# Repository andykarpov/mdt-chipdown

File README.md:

# MicroDEXED Touch Chipdown custom edition

This is an attempt to create a custom PCB of the MicroDEXED Touch (MDT) project to satisfy my own requirements:

- No modules, all chips should be soldered on PCB
- Avoid THT components as much as possible

**Warning! Work in progress. The revB is untested and unreleased yet.**

- Current tested revision: **revA**
- Current dev revision: **revB**

## PCB changelog & ERRATA:

- revA - initial revision
    - Note: Jumpers to select MIDI IN/OUT standard should be removed, instead of them please use 0 Ohm resistors
    - Latest revA contains the following changes: jumpers replaced with solder jumpers
    - The overall display height is slightly higher than expected. Please use 8.5mm standoffs for it. Also the plastic housing from the display pin headers should be removed and the pin height should be reduced to fit the desired connection height of 8.5mm
- revB:
    - 4-layers PCB
    - Replaced teensy module with a set of chips
    - Added additional SD card
    - Added additional LED from the supplementary MCU
    - Changed USB Host power path

## Rev.A Renders

## Case for rev.A

## Rev.B Renders

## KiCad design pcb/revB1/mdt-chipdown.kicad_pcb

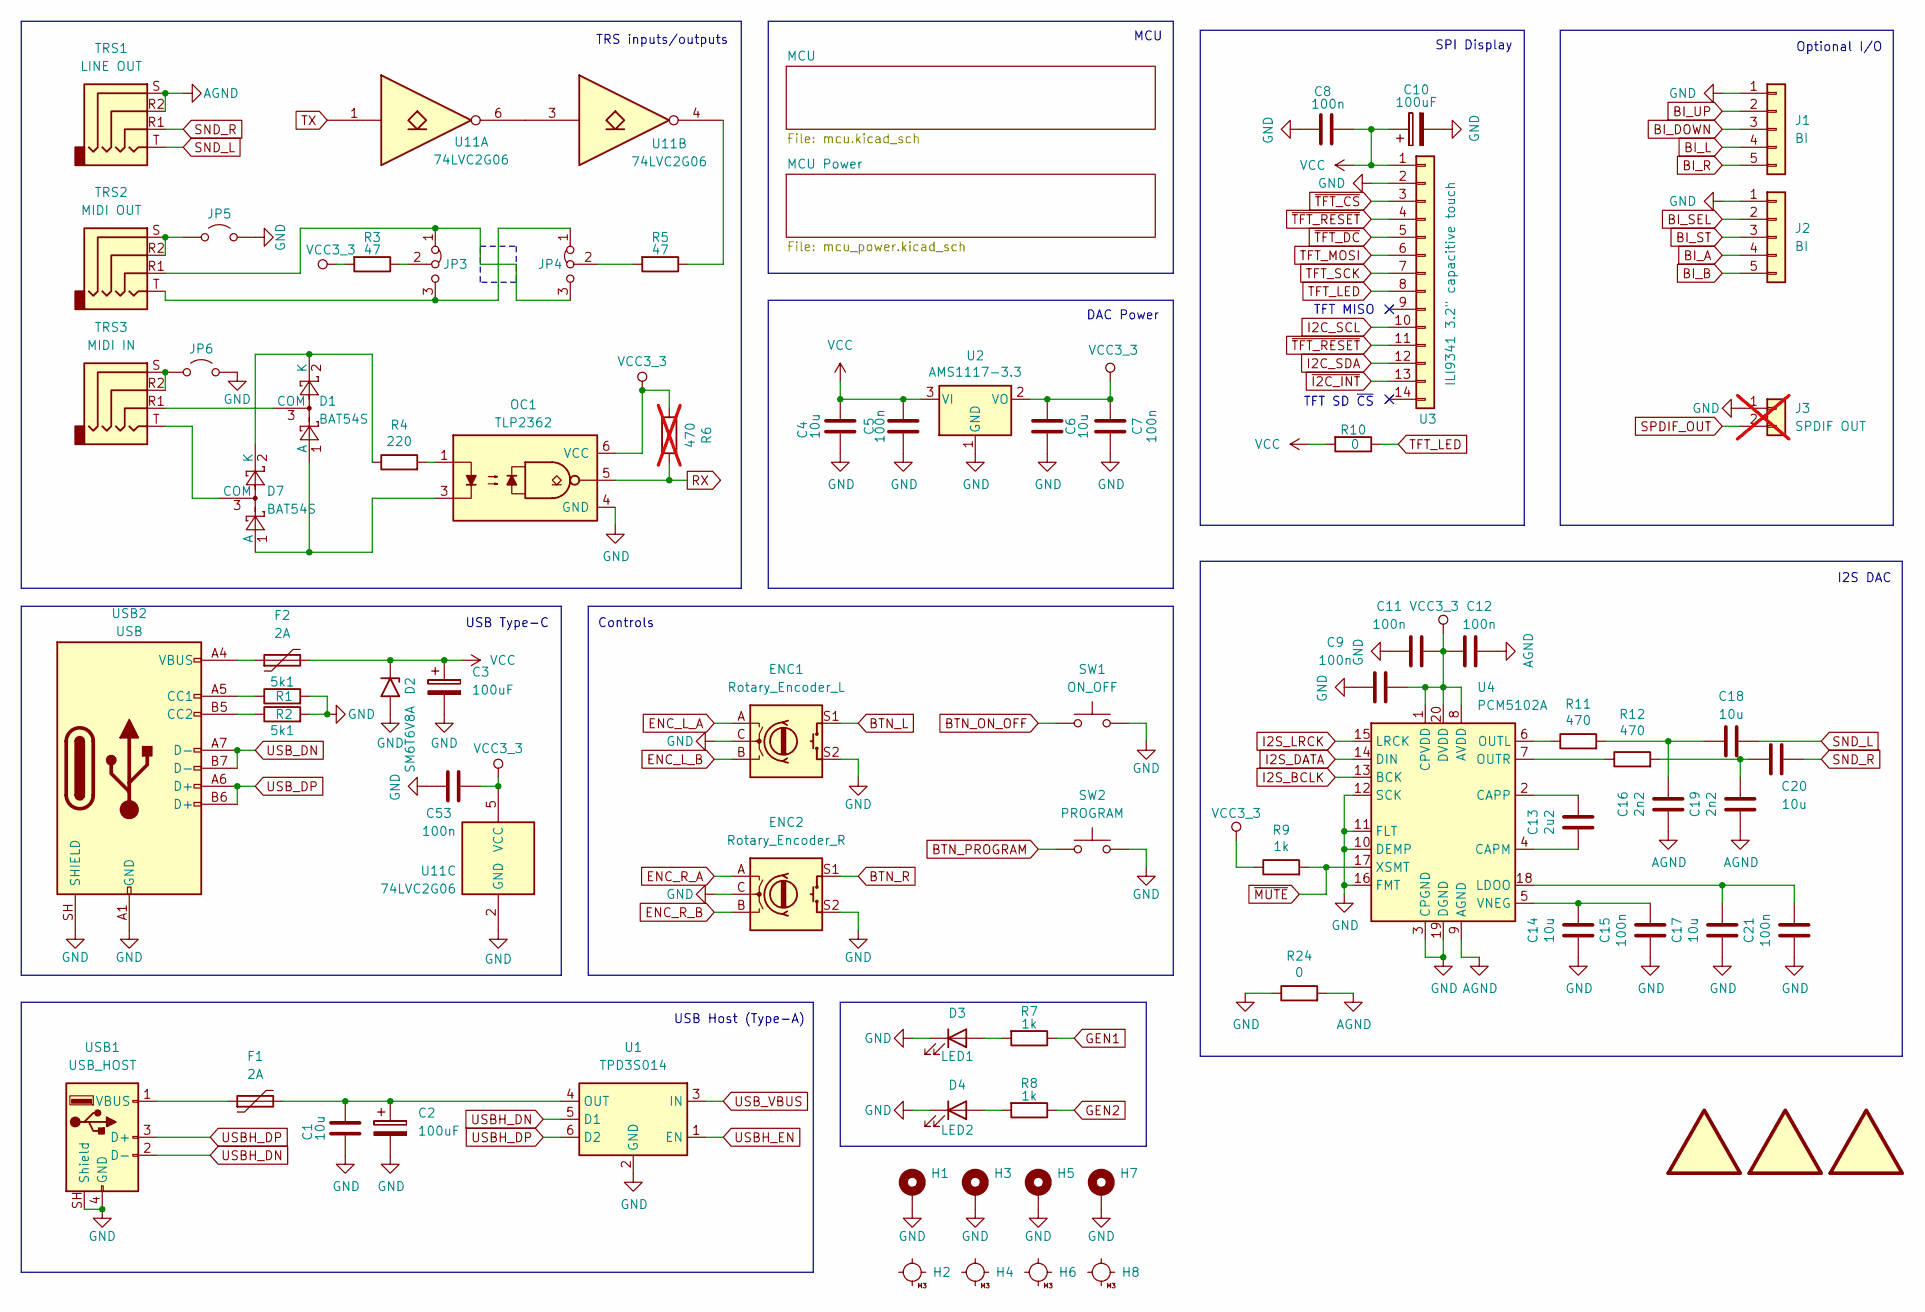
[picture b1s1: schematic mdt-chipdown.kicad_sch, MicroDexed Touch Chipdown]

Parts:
C1, C4, C6, C14, C17, C18, C20: 10u; C_0805_2012Metric_Pad1.18x1.45mm_HandSolder; LCSC C15850
C2, C3: 100uF; CP_EIA-7343-31_Kemet-D_HandSolder; LCSC C2749
C5, C7, C8, C9, C11, C12, C15, C21, C53: 100n; C_0805_2012Metric_Pad1.18x1.45mm_HandSolder; LCSC C1711
C10: 100uF; CP_EIA-6032-28_Kemet-C_HandSolder; LCSC C8649
C13: 2u2; C_0805_2012Metric_Pad1.18x1.45mm_HandSolder; LCSC C19110
C16, C19: 2n2; C_0805_2012Metric_Pad1.18x1.45mm_HandSolder; LCSC C1728
D1, D7: BAT54S; SOT-23_Handsoldering; LCSC C7420333
D2: SM6T6V8A; D_SMB_Handsoldering; LCSC C511038
D3: LED1; LED_Indicator_D3.0mm_W4.6mm_L6.5mm; LCSC C17683617
D4: LED2; LED_Indicator_D3.0mm_W4.6mm_L6.5mm; LCSC C473837
ENC1: Rotary_Encoder_L; RotaryEncoder_Alps_EC11E-Switch_Vertical_H20mm; LCSC C7435302
ENC2: Rotary_Encoder_R; RotaryEncoder_Alps_EC11E-Switch_Vertical_H20mm; LCSC C7435302
F1, F2: 2A; Fuse_1812_4532Metric_Pad1.30x3.40mm_HandSolder; LCSC C20812
H1, H3, H5, H7: MountingHole_Pad; MountingHole_3mm_Pad_Via
H2, H4, H6, H8: MountingHole_M3
J1, J2: BI; PinHeader_1x05_P2.54mm_Vertical; LCSC C5156614
J3: SPDIF OUT; Pin_Header_Straight_1x02; Part Number 1-0201FBV0T; LCSC C5360898; not fitted
JP3, JP4: Jumper_3_Bridged12; SolderJumper-3_P1.3mm_Bridged12_RoundedPad1.0x1.5mm
JP5: Jumper_2_Open; SolderJumper-2_P1.3mm_Bridged_RoundedPad1.0x1.5mm
JP6: Jumper_2_Open; SolderJumper-2_P1.3mm_Open_RoundedPad1.0x1.5mm
LOGO1: logo; microDXD_logo12
LOGO2: logo; andy_karpov_logo5_silk
LOGO3: logo; KiCad-Logo2_6mm_SilkScreen
OC1: TLP2362; SO-5-6_4.55x3.7mm_P1.27mm; LCSC C37658
R1, R2: 5k1; R_0805_2012Metric_Pad1.20x1.40mm_HandSolder; LCSC C26023
R3, R5: 47; R_0805_2012Metric_Pad1.20x1.40mm_HandSolder; LCSC C25315
R4: 220; R_0805_2012Metric_Pad1.20x1.40mm_HandSolder; LCSC C17557
R6: 470; R_0805_2012Metric_Pad1.20x1.40mm_HandSolder; LCSC C17710; not fitted
R7, R8, R9: 1k; R_0805_2012Metric_Pad1.20x1.40mm_HandSolder; LCSC C17513
R10: 0; R_0805_2012Metric_Pad1.20x1.40mm_HandSolder; LCSC C17477
R11, R12: 470; R_0805_2012Metric_Pad1.20x1.40mm_HandSolder; LCSC C17710
R24: 0; R_0805_2012Metric_Pad1.20x1.40mm_HandSolder; LCSC C17513
SW1: ON_OFF; Push_PTH_RA_8-020_h7.5mm; LCSC C125050
SW2: PROGRAM; Push_PTH_RA_8-020_h7.5mm; LCSC C125050
TRS1: LINE OUT; AUDIO_JACK_3.5MM_SMD_TRRS_rounded_mixed; LCSC C53447038
TRS2: MIDI OUT; AUDIO_JACK_3.5MM_SMD_TRRS_rounded_mixed; LCSC C53447038
TRS3: MIDI IN; AUDIO_JACK_3.5MM_SMD_TRRS_rounded_mixed; LCSC C53447038
U1: TPD3S014; SOT-23-6_Handsoldering; LCSC C87384
U2: AMS1117-3.3; TO-252-2; LCSC C41414107
U3: ILI9341 3.2" capacitive touch; PinSocket_1x14_P2.54mm_Vertical; LCSC C124407
U4: PCM5102A; TSSOP-20_4.4x6.5mm_P0.65mm; LCSC C107671
U11: 74LVC2G06; SOT-23-6_Handsoldering; LCSC C402162
USB1: USB_HOST; USB_A_Molex_67643_Horizontal; LCSC C2346
USB2: USB; USB_C_Receptacle_G-Switch_GT-USB-7010ASV; LCSC C165948

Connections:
AGND: C12.1, C16.1, C19.1, R24.2, TRS1.R2, TRS1.S, U4.9 (AGND)
BI_A: J2.4; also elsewhere on the board
BI_B: J2.5; also elsewhere on the board
BI_DOWN: J1.3; also elsewhere on the board
BI_L: J1.4; also elsewhere on the board
BI_R: J1.5; also elsewhere on the board
BI_SEL: J2.2; also elsewhere on the board
BI_ST: J2.3; also elsewhere on the board
BI_UP: J1.2; also elsewhere on the board
BTN_L: ENC1.S1; also elsewhere on the board
BTN_ON_OFF: SW1.1; also elsewhere on the board
BTN_PROGRAM: SW2.1; also elsewhere on the board
BTN_R: ENC2.S1; also elsewhere on the board
ENC_L_A: ENC1.A; also elsewhere on the board
ENC_L_B: ENC1.B; also elsewhere on the board
ENC_R_A: ENC2.A; also elsewhere on the board
ENC_R_B: ENC2.B; also elsewhere on the board
GEN1: R7.1; also elsewhere on the board
GEN2: R8.1; also elsewhere on the board
GND: C1.2, C2.2, C3.2, C4.2, C5.2, C6.2, C7.2, C8.2, C9.2, C10.2, C11.2, C14.1, C15.1, C17.1, C21.1, C53.2, D2.2 (A2), D3.1 (K), D4.1 (K), ENC1.C, ENC1.S2, ENC2.C, ENC2.S2, H1.1 (1_1), H3.1 (1_1), H5.1 (1_1), H7.1 (1_1), J1.1, J2.1, J3.1, JP5.2 (B), JP6.2 (B), OC1.4 (GND), R1.2, R2.2, R24.1, SW1.2, SW2.2, U1.2 (GND), U2.1 (GND), U3.2, U4.3 (CPGND), U4.10 (DEMP), U4.11 (FLT), U4.12 (SCK), U4.16 (FMT), U4.19 (DGND), U11.2 (GND), USB1.4 (GND), USB1.SH (Shield), USB2.A1 (GND), USB2.A12 (GND), USB2.B1 (GND), USB2.B12 (GND), USB2.SH (SHIELD); also elsewhere on the board
I2C_SCL: U3.10; also elsewhere on the board
I2C_SDA: U3.12; also elsewhere on the board
I2S_BCLK: U4.13 (BCK); also elsewhere on the board
I2S_DATA: U4.14 (DIN); also elsewhere on the board
I2S_LRCK: U4.15 (LRCK); also elsewhere on the board
unnamed: C16.2, C18.2, R11.2
unnamed: C19.2, C20.2, R12.2
unnamed: D1.1 (A), D7.1 (A), OC1.3
unnamed: D1.3 (COM), TRS3.R1
unnamed: D1.2 (K), D7.2 (K), R4.1
unnamed: D3.2 (A), R7.2
unnamed: D4.2 (A), R8.2
unnamed: D7.3 (COM), TRS3.T
unnamed: F2.1, USB2.A4 (VBUS), USB2.A9 (VBUS), USB2.B4 (VBUS), USB2.B9 (VBUS)
unnamed: JP3.1 (A), JP4.3 (B), TRS2.R1
unnamed: JP3.3 (B), JP4.1 (A), TRS2.T
unnamed: JP3.2 (C), R3.1
unnamed: JP4.2 (C), R5.2
unnamed: JP5.1 (A), TRS2.R2, TRS2.S
unnamed: JP6.1 (A), TRS3.R2, TRS3.S
unnamed: OC1.1, R4.2
unnamed: R5.1, U11.4
unnamed: C1.1, C2.1, F1.2, U1.4 (OUT)
unnamed: C13.1, U4.4 (CAPM)
unnamed: C13.2, U4.2 (CAPP)
unnamed: C17.2, C21.2, U4.18 (LDOO)
unnamed: R11.1, U4.6 (OUTL)
unnamed: R12.1, U4.7 (OUTR)
unnamed: C14.2, C15.2, U4.5 (VNEG)
unnamed: U11.3, U11.6
unnamed: F1.1, USB1.1 (VBUS)
unnamed: R1.1, USB2.A5 (CC1)
unnamed: R2.1, USB2.B5 (CC2)
RX: OC1.5, R6.2; also elsewhere on the board
SND_L: C18.1, TRS1.T
SND_R: C20.1, TRS1.R1
SPDIF_OUT: J3.2; also elsewhere on the board
TFT_LED: R10.1, U3.8
TFT_MOSI: U3.6; also elsewhere on the board
TFT_SCK: U3.7; also elsewhere on the board
TX: U11.1; also elsewhere on the board
USBH_DN: U1.5 (D1), USB1.2 (D-); also elsewhere on the board
USBH_DP: U1.6 (D2), USB1.3 (D+); also elsewhere on the board
USBH_EN: U1.1 (EN); also elsewhere on the board
USB_DN: USB2.A7 (D-), USB2.B7 (D-); also elsewhere on the board
USB_DP: USB2.A6 (D+), USB2.B6 (D+); also elsewhere on the board
USB_VBUS: U1.3 (IN); also elsewhere on the board
VCC: C3.1, C4.1, C5.1, C8.1, C10.1, D2.1 (A1), F2.2, R10.2, U2.3 (VI), U3.1; also elsewhere on the board
VCC3_3: C6.1, C7.1, C9.1, C11.1, C12.2, C53.1, OC1.6 (VCC), R3.2, R6.1, R9.1, U2.2 (VO), U4.1 (CPVDD), U4.8 (AVDD), U4.20 (DVDD), U11.5 (VCC)
~I2C_INT: U3.13; also elsewhere on the board
~MUTE: R9.2, U4.17 (XSMT); also elsewhere on the board
~TFT_CS: U3.3; also elsewhere on the board
~TFT_DC: U3.5; also elsewhere on the board
~TFT_RESET: U3.4, U3.11; also elsewhere on the board

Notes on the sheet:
TRS inputs/outputs
I2S DAC
TFT SD ~{CS}
DAC Power
MCU
Optional I/O
SPI Display
TFT MISO
USB Host (Type-A)
Controls
USB Type-C

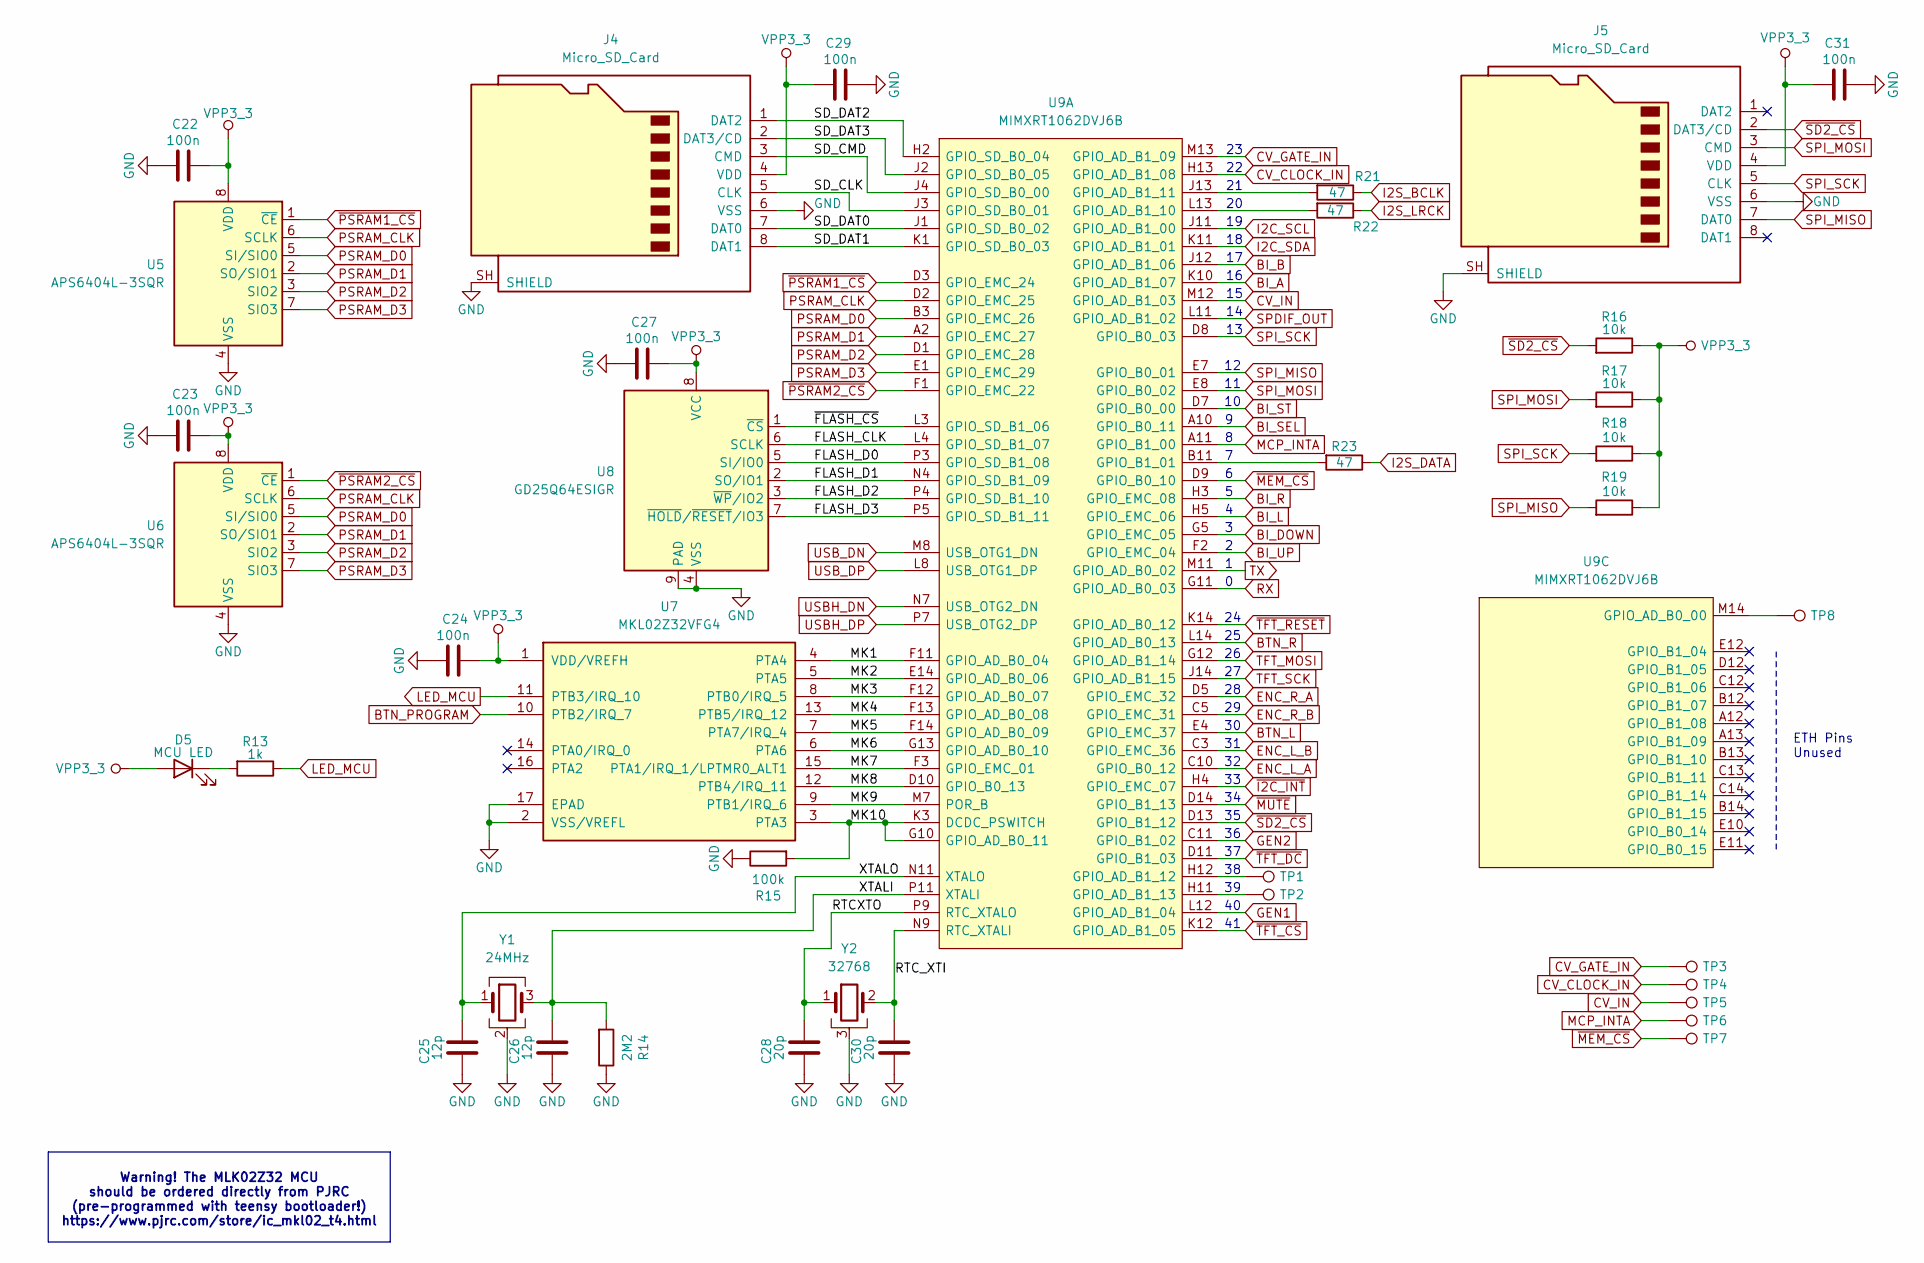
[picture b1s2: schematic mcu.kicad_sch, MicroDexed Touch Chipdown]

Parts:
C22, C23, C24, C27, C29, C31: 100n; C_0805_2012Metric_Pad1.18x1.45mm_HandSolder; LCSC C1711
C25, C26: 12p; C_0805_2012Metric_Pad1.18x1.45mm_HandSolder; LCSC C152848
C28, C30: 20p; C_0805_2012Metric_Pad1.18x1.45mm_HandSolder; LCSC C1727
D5: MCU LED; LED_Indicator_D3.0mm_W4.6mm_L6.5mm; LCSC C19188468
J4, J5: Micro_SD_Card; GCT-MEM2055-00-190-01-A; LCSC C91145
R13: 1k; R_0805_2012Metric_Pad1.20x1.40mm_HandSolder; LCSC C17513
R14: 2M2; R_0805_2012Metric_Pad1.20x1.40mm_HandSolder; LCSC C26113
R15: 100k; R_0805_2012Metric_Pad1.20x1.40mm_HandSolder; LCSC C25611
R16, R17, R18, R19: 10k; R_0805_2012Metric_Pad1.20x1.40mm_HandSolder; LCSC C17414
R21, R22, R23: 47; R_0805_2012Metric_Pad1.20x1.40mm_HandSolder; LCSC C25315
TP1: GPIO_AD_B1_12; TestPoint_Pad_2.0x2.0mm
TP2: GPIO_AD_B1_13; TestPoint_Pad_2.0x2.0mm
TP3: CV GATE IN; TestPoint_Pad_2.0x2.0mm
TP4: CV CLOCK IN; TestPoint_Pad_2.0x2.0mm
TP5: CV IN; TestPoint_Pad_2.0x2.0mm
TP6: MCP INTA; TestPoint_Pad_2.0x2.0mm
TP7: MEM CS; TestPoint_Pad_2.0x2.0mm
TP8: GPIO_AD_B0_00; TestPoint_Pad_2.0x2.0mm
U5, U6: APS6404L-3SQR; SOIC-8_3.9x4.9mm_P1.27mm; LCSC C5333729
U7: MKL02Z32VFG4; QFN-16-1EP_3x3mm_P0.5mm_EP1.9x1.9mm; LCSC C2056583
U8: GD25Q64ESIGR; SOIC-8_5.3x5.3mm_P1.27mm; LCSC C2831359
U9: MIMXRT1062DVJ6B; BGA196C80P14X14_1200X1200X152; Mouser Part Number 771-MIMXRT1062DVJ6B
Y1: 24MHz; Crystal_SMD_3225-4Pin_3.2x2.5mm_HandSoldering; LCSC C15643
Y2: 32768; Crystal_C26-LF_D2.1mm_L6.5mm_Horizontal_1EP_style2; LCSC C2236

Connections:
/MCU/FLASH_CLK: U8.6 (SCLK), U9.L4 (GPIO_SD_B1_07)
/MCU/FLASH_D0: U8.5 (SI/IO0), U9.P3 (GPIO_SD_B1_08)
/MCU/FLASH_D1: U8.2 (SO/IO1), U9.N4 (GPIO_SD_B1_09)
/MCU/FLASH_D2: U8.3 (~WP/IO2), U9.P4 (GPIO_SD_B1_10)
/MCU/FLASH_D3: U8.7 (~HOLD/~RESET/IO3), U9.P5 (GPIO_SD_B1_11)
/MCU/MK1: U7.4 (PTA4), U9.F11 (GPIO_AD_B0_04)
/MCU/MK2: U7.5 (PTA5), U9.E14 (GPIO_AD_B0_06)
/MCU/MK3: U7.8 (PTB0/IRQ_5), U9.F12 (GPIO_AD_B0_07)
/MCU/MK4: U7.13 (PTB5/IRQ_12), U9.F13 (GPIO_AD_B0_08)
/MCU/MK5: U7.7 (PTA7/IRQ_4), U9.F14 (GPIO_AD_B0_09)
/MCU/MK6: U7.6 (PTA6), U9.G13 (GPIO_AD_B0_10)
/MCU/MK7: U7.15 (PTA1/IRQ_1/LPTMR0_ALT1), U9.F3 (GPIO_EMC_01)
/MCU/MK8: U7.12 (PTB4/IRQ_11), U9.D10 (GPIO_B0_13)
/MCU/MK9: U7.9 (PTB1/IRQ_6), U9.M7 (POR_B)
/MCU/MK10: R15.2, U7.3 (PTA3), U9.G10 (GPIO_AD_B0_11), U9.K3 (DCDC_PSWITCH)
/MCU/RTCXTO: C28.1, U9.P9 (RTC_XTALO), Y2.1
/MCU/RTC_XTI: C30.1, U9.N9 (RTC_XTALI), Y2.2
/MCU/SD_CLK: J4.5 (CLK), U9.J3 (GPIO_SD_B0_01)
/MCU/SD_CMD: J4.3 (CMD), U9.J4 (GPIO_SD_B0_00)
/MCU/SD_DAT0: J4.7 (DAT0), U9.J1 (GPIO_SD_B0_02)
/MCU/SD_DAT1: J4.8 (DAT1), U9.K1 (GPIO_SD_B0_03)
/MCU/SD_DAT2: J4.1 (DAT2), U9.H2 (GPIO_SD_B0_04)
/MCU/SD_DAT3: J4.2 (DAT3/CD), U9.J2 (GPIO_SD_B0_05)
/MCU/XTALI: C26.1, R14.2, U9.P11 (XTALI), Y1.3
/MCU/XTALO: C25.1, U9.N11 (XTALO), Y1.1
/MCU/~FLASH_CS: U8.1 (~CS), U9.L3 (GPIO_SD_B1_06)
BI_A: U9.K10 (GPIO_AD_B1_07); also elsewhere on the board
BI_B: U9.J12 (GPIO_AD_B1_06); also elsewhere on the board
BI_DOWN: U9.G5 (GPIO_EMC_05); also elsewhere on the board
BI_L: U9.H5 (GPIO_EMC_06); also elsewhere on the board
BI_R: U9.H3 (GPIO_EMC_08); also elsewhere on the board
BI_SEL: U9.A10 (GPIO_B0_11); also elsewhere on the board
BI_ST: U9.D7 (GPIO_B0_00); also elsewhere on the board
BI_UP: U9.F2 (GPIO_EMC_04); also elsewhere on the board
BTN_L: U9.E4 (GPIO_EMC_37); also elsewhere on the board
BTN_PROGRAM: U7.10 (PTB2/IRQ_7); also elsewhere on the board
BTN_R: U9.L14 (GPIO_AD_B0_13); also elsewhere on the board
CV_CLOCK_IN: TP4.1 (1_1), U9.H13 (GPIO_AD_B1_08)
CV_GATE_IN: TP3.1 (1_1), U9.M13 (GPIO_AD_B1_09)
CV_IN: TP5.1 (1_1), U9.M12 (GPIO_AD_B1_03)
ENC_L_A: U9.C10 (GPIO_B0_12); also elsewhere on the board
ENC_L_B: U9.C3 (GPIO_EMC_36); also elsewhere on the board
ENC_R_A: U9.D5 (GPIO_EMC_32); also elsewhere on the board
ENC_R_B: U9.C5 (GPIO_EMC_31); also elsewhere on the board
GEN1: U9.L12 (GPIO_AD_B1_04); also elsewhere on the board
GEN2: U9.C11 (GPIO_B1_02); also elsewhere on the board
GND: C22.2, C23.2, C24.2, C25.2, C26.2, C27.2, C28.2, C29.2, C30.2, C31.2, J4.6 (VSS), J4.SH (SHIELD), J5.6 (VSS), J5.SH (SHIELD), R14.1, R15.1, U5.4 (VSS), U6.4 (VSS), U7.2 (VSS/VREFL), U7.17 (EPAD), U8.4 (VSS), U8.9 (PAD), Y1.2 (G), Y1.4 (G), Y2.3; also elsewhere on the board
I2C_SCL: U9.J11 (GPIO_AD_B1_00); also elsewhere on the board
I2C_SDA: U9.K11 (GPIO_AD_B1_01); also elsewhere on the board
I2S_BCLK: R21.1; also elsewhere on the board
I2S_DATA: R23.1; also elsewhere on the board
I2S_LRCK: R22.1; also elsewhere on the board
LED_MCU: R13.1, U7.11 (PTB3/IRQ_10)
MCP_INTA: TP6.1 (1_1), U9.A11 (GPIO_B1_00)
unnamed: D5.1 (K), R13.2
unnamed: R22.2, U9.L13 (GPIO_AD_B1_10)
unnamed: R21.2, U9.J13 (GPIO_AD_B1_11)
unnamed: TP1.1 (1_1), U9.H12 (GPIO_AD_B1_12)
unnamed: TP2.1 (1_1), U9.H11 (GPIO_AD_B1_13)
unnamed: R23.2, U9.B11 (GPIO_B1_01)
unnamed: TP8.1 (1_1), U9.M14 (GPIO_AD_B0_00)
PSRAM_CLK: U5.6 (SCLK), U6.6 (SCLK), U9.D2 (GPIO_EMC_25)
PSRAM_D0: U5.5 (SI/SIO0), U6.5 (SI/SIO0), U9.B3 (GPIO_EMC_26)
PSRAM_D1: U5.2 (SO/SIO1), U6.2 (SO/SIO1), U9.A2 (GPIO_EMC_27)
PSRAM_D2: U5.3 (SIO2), U6.3 (SIO2), U9.D1 (GPIO_EMC_28)
PSRAM_D3: U5.7 (SIO3), U6.7 (SIO3), U9.E1 (GPIO_EMC_29)
RX: U9.G11 (GPIO_AD_B0_03); also elsewhere on the board
SPDIF_OUT: U9.L11 (GPIO_AD_B1_02); also elsewhere on the board
SPI_MISO: J5.7 (DAT0), R19.2, U9.E7 (GPIO_B0_01)
SPI_MOSI: J5.3 (CMD), R17.2, U9.E8 (GPIO_B0_02)
SPI_SCK: J5.5 (CLK), R18.2, U9.D8 (GPIO_B0_03)
TFT_MOSI: U9.G12 (GPIO_AD_B1_14); also elsewhere on the board
TFT_SCK: U9.J14 (GPIO_AD_B1_15); also elsewhere on the board
TX: U9.M11 (GPIO_AD_B0_02); also elsewhere on the board
USBH_DN: U9.N7 (USB_OTG2_DN); also elsewhere on the board
USBH_DP: U9.P7 (USB_OTG2_DP); also elsewhere on the board
USB_DN: U9.M8 (USB_OTG1_DN); also elsewhere on the board
USB_DP: U9.L8 (USB_OTG1_DP); also elsewhere on the board
VPP3_3: C22.1, C23.1, C24.1, C27.1, C29.1, C31.1, D5.2 (A), J4.4 (VDD), J5.4 (VDD), R16.1, R17.1, R18.1, R19.1, U5.8 (VDD), U6.8 (VDD), U7.1 (VDD/VREFH), U8.8 (VCC); also elsewhere on the board
~I2C_INT: U9.H4 (GPIO_EMC_07); also elsewhere on the board
~MEM_CS: TP7.1 (1_1), U9.D9 (GPIO_B0_10)
~MUTE: U9.D14 (GPIO_B1_13); also elsewhere on the board
~PSRAM1_CS: U5.1 (~CE), U9.D3 (GPIO_EMC_24)
~PSRAM2_CS: U6.1 (~CE), U9.F1 (GPIO_EMC_22)
~SD2_CS: J5.2 (DAT3/CD), R16.2, U9.D13 (GPIO_B1_12)
~TFT_CS: U9.K12 (GPIO_AD_B1_05); also elsewhere on the board
~TFT_DC: U9.D11 (GPIO_B1_03); also elsewhere on the board
~TFT_RESET: U9.K14 (GPIO_AD_B0_12); also elsewhere on the board

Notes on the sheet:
Warning! The MLK02Z32 MCU should be ordered directly from PJRC (pre-programmed with teensy bootloader!) https://www.pjrc.com/store/ic_mkl02_t4.html
ETH Pins Unused

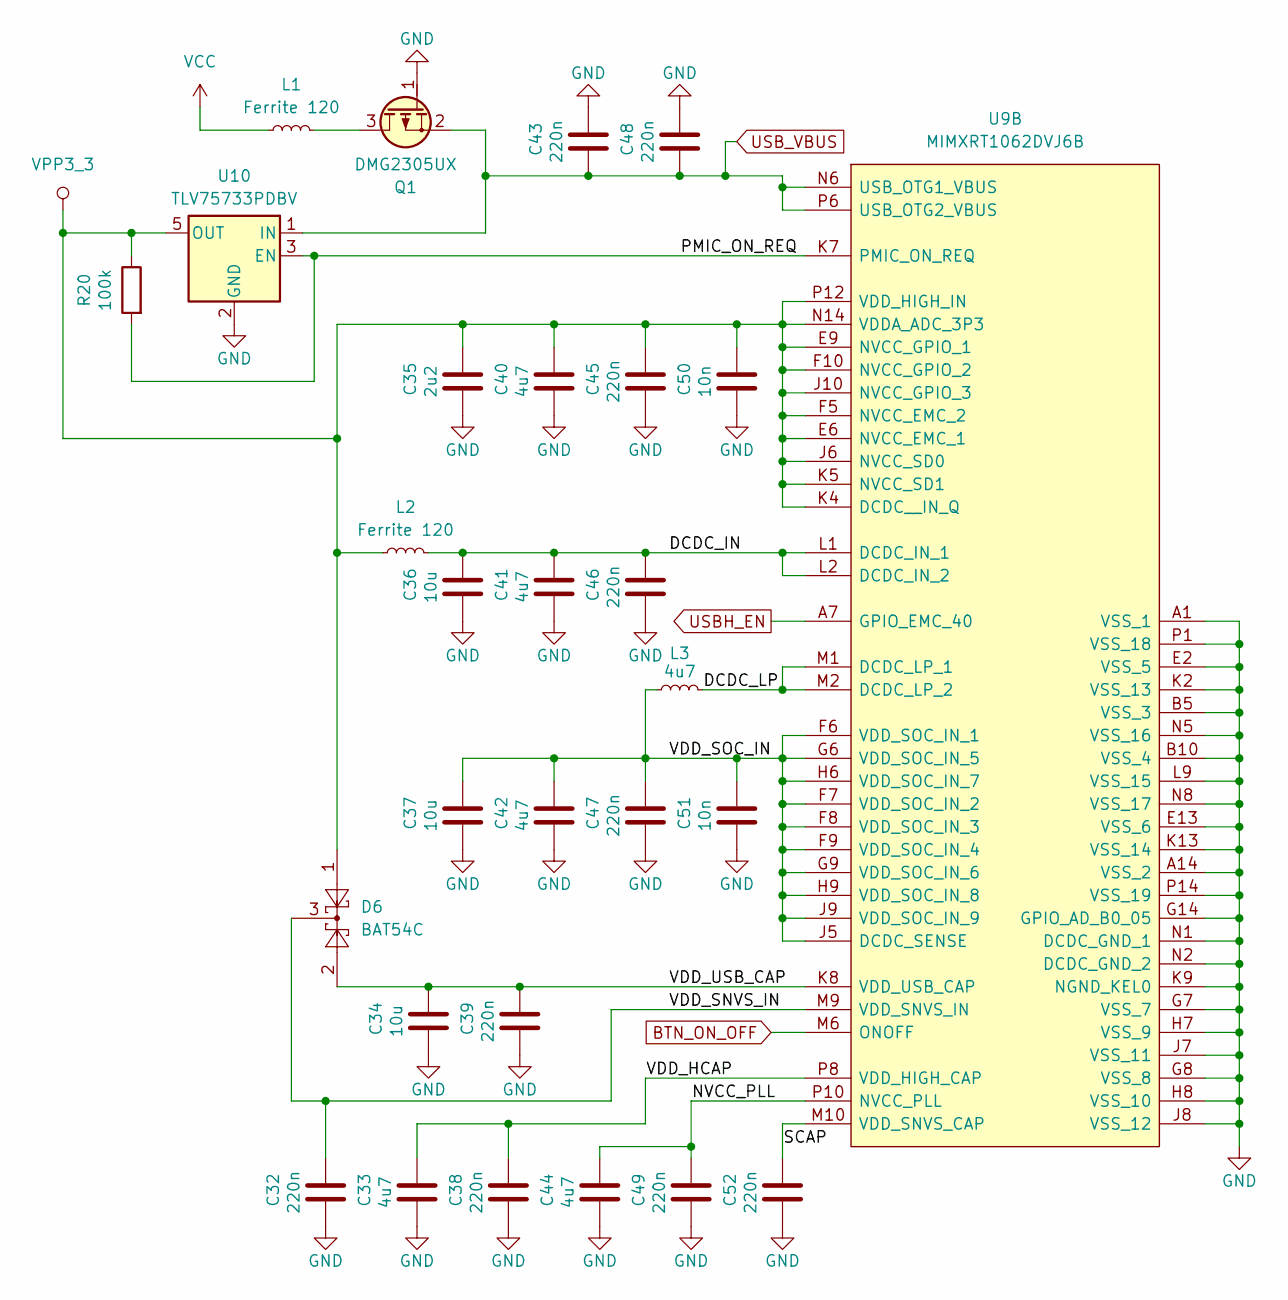
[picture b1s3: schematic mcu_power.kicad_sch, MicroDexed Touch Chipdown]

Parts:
C32, C38, C39, C43, C45, C46, C48, C49, C52: 220n; C_0805_2012Metric_Pad1.18x1.45mm_HandSolder; LCSC C5378
C33, C40, C41, C44: 4u7; C_0805_2012Metric_Pad1.18x1.45mm_HandSolder; LCSC C1779
C34, C36: 10u; C_0805_2012Metric_Pad1.18x1.45mm_HandSolder; LCSC C15850
C35: 2u2; C_0805_2012Metric_Pad1.18x1.45mm_HandSolder; LCSC C19110
C37: 10u; C_0805_2012Metric; LCSC C1713
C42: 4u7; C_0805_2012Metric; LCSC C1779
C47: 220n; C_0805_2012Metric; LCSC C5378
C50: 10n; C_0805_2012Metric_Pad1.18x1.45mm_HandSolder; LCSC C1710
C51: 10n; C_0805_2012Metric; LCSC C1710
D6: BAT54C; SOT-23_Handsoldering; LCSC C37704
L1, L2: Ferrite 120; L_0805_2012Metric_Pad1.15x1.40mm_HandSolder; LCSC C5671
L3: 4u7; L_0805_2012Metric_Pad1.15x1.40mm; LCSC C63166
Q1: DMG2305UX; SOT-23_Handsoldering; LCSC C144153
R20: 100k; R_0805_2012Metric_Pad1.20x1.40mm_HandSolder; LCSC C25611
U9: MIMXRT1062DVJ6B; BGA196C80P14X14_1200X1200X152; Mouser Part Number 771-MIMXRT1062DVJ6B
U10: TLV75733PDBV; SOT-23-5_HandSoldering; LCSC C485517

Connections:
/MCU Power/DCDC_IN: C36.1, C41.1, C46.1, L2.2, U9.L1 (DCDC_IN_1), U9.L2 (DCDC_IN_2)
/MCU Power/DCDC_LP: L3.2, U9.M1 (DCDC_LP_1), U9.M2 (DCDC_LP_2)
/MCU Power/NVCC_PLL: C44.1, C49.1, U9.P10 (NVCC_PLL)
/MCU Power/PMIC_ON_REQ: R20.2, U9.K7 (PMIC_ON_REQ), U10.3 (EN)
/MCU Power/SCAP: C52.1, U9.M10 (VDD_SNVS_CAP)
/MCU Power/VDD_HCAP: C33.1, C38.1, U9.P8 (VDD_HIGH_CAP)
/MCU Power/VDD_SNVS_IN: C32.1, D6.3, U9.M9 (VDD_SNVS_IN)
/MCU Power/VDD_SOC_IN: C37.1, C42.1, C47.1, C51.1, L3.1, U9.F6 (VDD_SOC_IN_1), U9.F7 (VDD_SOC_IN_2), U9.F8 (VDD_SOC_IN_3), U9.F9 (VDD_SOC_IN_4), U9.G6 (VDD_SOC_IN_5), U9.G9 (VDD_SOC_IN_6), U9.H6 (VDD_SOC_IN_7), U9.H9 (VDD_SOC_IN_8), U9.J5 (DCDC_SENSE), U9.J9 (VDD_SOC_IN_9)
/MCU Power/VDD_USB_CAP: C34.1, C39.1, D6.2, U9.K8 (VDD_USB_CAP)
BTN_ON_OFF: U9.M6 (ONOFF); also elsewhere on the board
GND: C32.2, C33.2, C34.2, C35.2, C36.2, C37.2, C38.2, C39.2, C40.2, C41.2, C42.2, C43.1, C44.2, C45.2, C46.2, C47.2, C48.1, C49.2, C50.2, C51.2, C52.2, Q1.1 (G), U9.A1 (VSS_1), U9.A14 (VSS_2), U9.B5 (VSS_3), U9.B10 (VSS_4), U9.E2 (VSS_5), U9.E13 (VSS_6), U9.G7 (VSS_7), U9.G8 (VSS_8), U9.G14 (GPIO_AD_B0_05), U9.H7 (VSS_9), U9.H8 (VSS_10), U9.J7 (VSS_11), U9.J8 (VSS_12), U9.K2 (VSS_13), U9.K9 (NGND_KEL0), U9.K13 (VSS_14), U9.L9 (VSS_15), U9.N1 (DCDC_GND_1), U9.N2 (DCDC_GND_2), U9.N5 (VSS_16), U9.N8 (VSS_17), U9.P1 (VSS_18), U9.P14 (VSS_19), U10.2 (GND); also elsewhere on the board
unnamed: L1.2, Q1.3 (D)
USBH_EN: U9.A7 (GPIO_EMC_40); also elsewhere on the board
USB_VBUS: C43.2, C48.2, Q1.2 (S), U9.N6 (USB_OTG1_VBUS), U9.P6 (USB_OTG2_VBUS), U10.1 (IN); also elsewhere on the board
VCC: L1.1; also elsewhere on the board
VPP3_3: C35.1, C40.1, C45.1, C50.1, D6.1, L2.1, R20.1, U9.E6 (NVCC_EMC_1), U9.E9 (NVCC_GPIO_1), U9.F5 (NVCC_EMC_2), U9.F10 (NVCC_GPIO_2), U9.J6 (NVCC_SD0), U9.J10 (NVCC_GPIO_3), U9.K4 (DCDC__IN_Q), U9.K5 (NVCC_SD1), U9.N14 (VDDA_ADC_3P3), U9.P12 (VDD_HIGH_IN), U10.5 (OUT); also elsewhere on the board

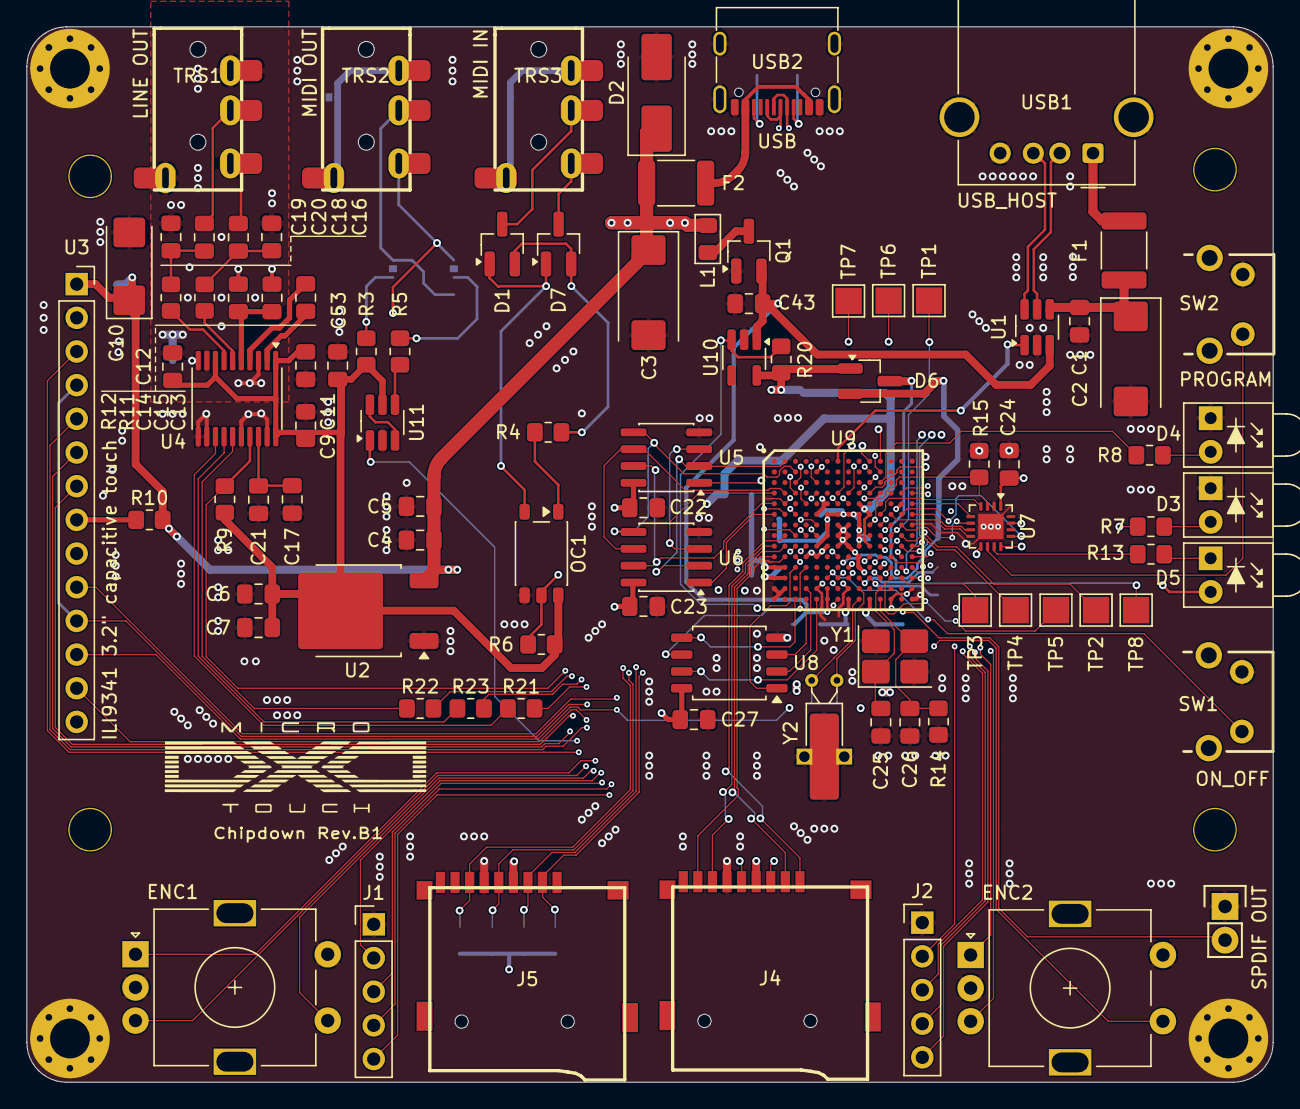
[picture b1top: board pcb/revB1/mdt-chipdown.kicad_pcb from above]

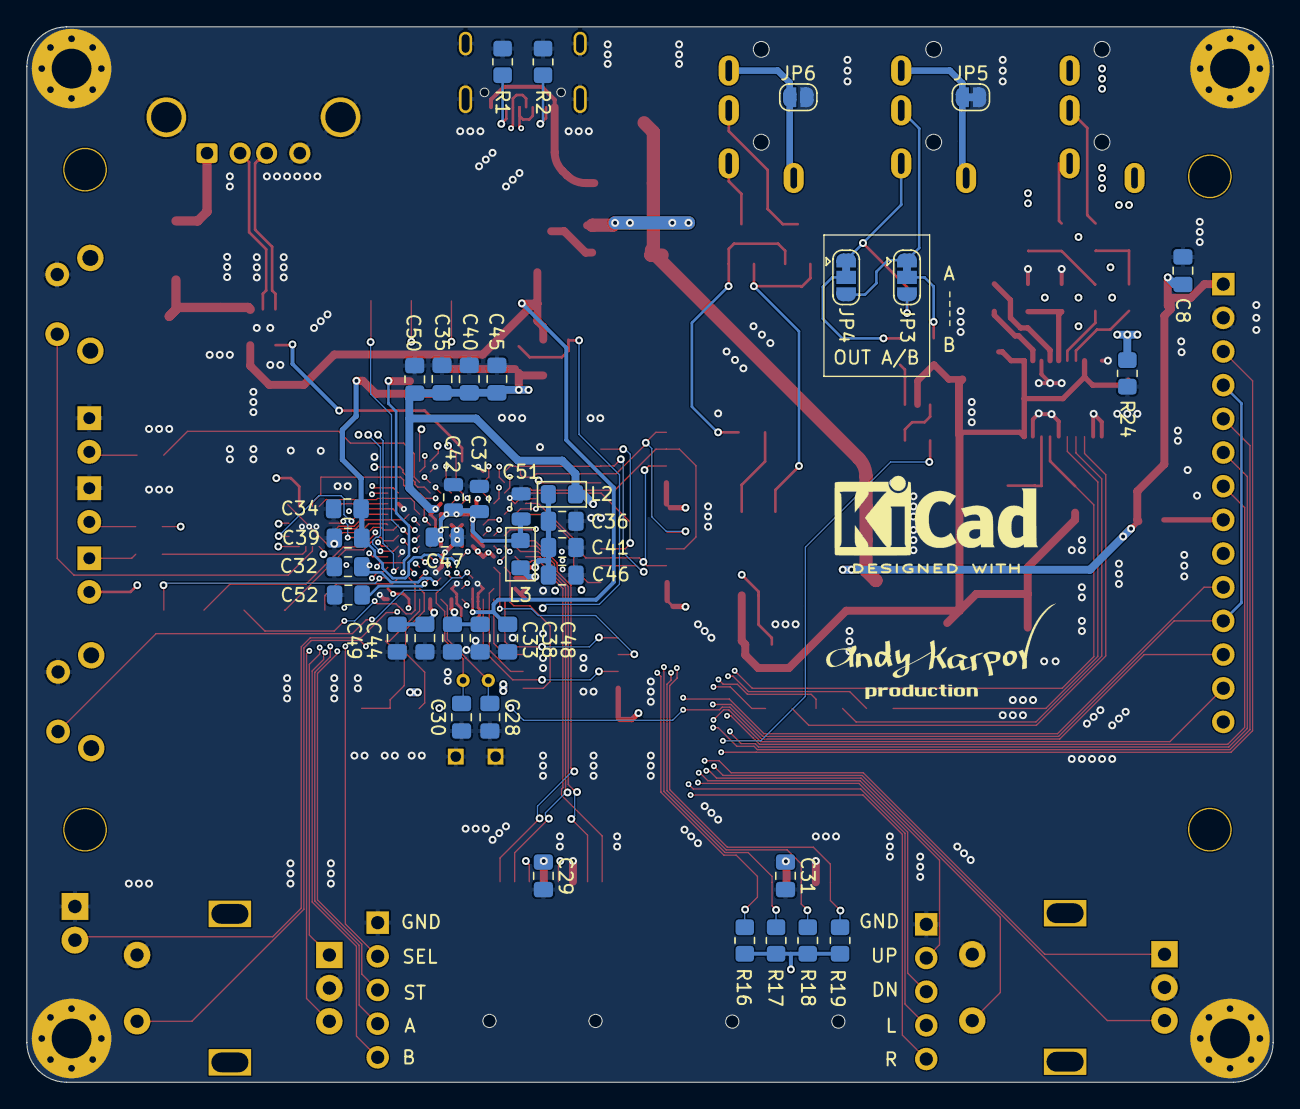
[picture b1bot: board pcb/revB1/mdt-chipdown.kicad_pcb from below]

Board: 4 copper layers, 94.0 x 79.6 mm, 141 parts (40 on the bottom side), 135 nets.

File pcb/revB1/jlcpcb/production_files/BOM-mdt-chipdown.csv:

Comment,Designator,Footprint,LCSC,Quantity
0,R10,R_0805_2012Metric_Pad1.20x1.40mm_HandSolder,C17477,1
100k,"R15,R20",R_0805_2012Metric_Pad1.20x1.40mm_HandSolder,C25611,2
100n,"C11,C12,C15,C21,C22,C23,C24,C27,C29,C31,C5,C53,C7,C8,C9",C_0805_2012Metric_Pad1.18x1.45mm_HandSolder,C1711,15
100uF,"C2,C3",CP_EIA-7343-31_Kemet-D_HandSolder,C2749,2
100uF,C10,CP_EIA-6032-28_Kemet-C_HandSolder,C8649,1
10k,"R16,R17,R18,R19",R_0805_2012Metric_Pad1.20x1.40mm_HandSolder,C17414,4
10n,"C50,C51",C_0805_2012Metric_Pad1.18x1.45mm_HandSolder,C1710,2
10u,"C1,C14,C17,C18,C20,C34,C36,C4,C6",C_0805_2012Metric_Pad1.18x1.45mm_HandSolder,C15850,9
10u,C37,C_0805_2012Metric,C1713,1
12p,"C25,C26",C_0805_2012Metric_Pad1.18x1.45mm_HandSolder,C152848,2
1k,"R13,R7,R8,R9",R_0805_2012Metric_Pad1.20x1.40mm_HandSolder,C17513,4
20p,"C28,C30",C_0805_2012Metric_Pad1.18x1.45mm_HandSolder,C1727,2
220,R4,R_0805_2012Metric_Pad1.20x1.40mm_HandSolder,C17557,1
220n,"C32,C38,C39,C43,C45,C46,C47,C48,C49,C52",C_0805_2012Metric_Pad1.18x1.45mm_HandSolder,C5378,10
24MHz,Y1,Crystal_SMD_3225-4Pin_3.2x2.5mm_HandSoldering,C15643,1
2A,"F1,F2",Fuse_1812_4532Metric_Pad1.30x3.40mm_HandSolder,C20812,2
2M2,R14,R_0805_2012Metric_Pad1.20x1.40mm_HandSolder,C26113,1
2n2,"C16,C19",C_0805_2012Metric_Pad1.18x1.45mm_HandSolder,C1728,2
2u2,"C13,C35",C_0805_2012Metric_Pad1.18x1.45mm_HandSolder,C19110,2
32768,Y2,Crystal_C26-LF_D2.1mm_L6.5mm_Horizontal_1EP_style2,C2236,1
47,"R3,R5",R_0805_2012Metric_Pad1.20x1.40mm_HandSolder,C25315,2
470,"R11,R12,R6",R_0805_2012Metric_Pad1.20x1.40mm_HandSolder,C17710,3
4u7,"C33,C40,C41,C42,C44",C_0805_2012Metric_Pad1.18x1.45mm_HandSolder,C1779,5
4u7,L3,L_0805_2012Metric_Pad1.15x1.40mm,C63166,1
5k1,"R1,R2",R_0805_2012Metric_Pad1.20x1.40mm_HandSolder,C26023,2
74LVC2G06,U11,SOT-23-6_Handsoldering,C402162,1
AMS1117-3.3,U2,TO-252-2,C41414107,1
APS6404L-3SQR,"U5,U6",SOIC-8_3.9x4.9mm_P1.27mm,C5333729,2
BAT54C,D6,SOT-23_Handsoldering,C37704,1
BAT54S,"D1,D7",SOT-23_Handsoldering,C7420333,2
BI,"J1,J2",PinHeader_1x05_P2.54mm_Vertical,C5156614,2
DMG2305UX,Q1,SOT-23_Handsoldering,C144153,1
Ferrite 120,"L1,L2",L_0805_2012Metric_Pad1.15x1.40mm_HandSolder,C5671,2
GD25Q64ESIGR,U8,SOIC-8_5.3x5.3mm_P1.27mm,C2831359,1
"ILI9341 3.2"" capacitive touch",U3,PinSocket_1x14_P2.54mm_Vertical,C124407,1
LED1,D3,LED_Indicator_D3.0mm_W4.6mm_L6.5mm,C17683617,1
LED2,D4,LED_Indicator_D3.0mm_W4.6mm_L6.5mm,C473837,1
LINE OUT,TRS1,AUDIO_JACK_3.5MM_SMD_TRRS_rounded_mixed,C53447038,1
MCU LED,D5,LED_Indicator_D3.0mm_W4.6mm_L6.5mm,C19188468,1
MIDI IN,TRS3,AUDIO_JACK_3.5MM_SMD_TRRS_rounded_mixed,C53447038,1
MIDI OUT,TRS2,AUDIO_JACK_3.5MM_SMD_TRRS_rounded_mixed,C53447038,1
MIMXRT1062DVJ6B,U9,BGA196C80P14X14_1200X1200X152,C3216699,1
MKL02Z32VFG4,U7,QFN-16-1EP_3x3mm_P0.5mm_EP1.9x1.9mm,C2056583,1
Micro_SD_Card,"J4,J5",GCT-MEM2055-00-190-01-A,C91145,2
ON_OFF,SW1,Push_PTH_RA_8-020_h7.5mm,C125050,1
PCM5102A,U4,TSSOP-20_4.4x6.5mm_P0.65mm,C107671,1
PROGRAM,SW2,Push_PTH_RA_8-020_h7.5mm,C125050,1
Rotary_Encoder_L,ENC1,RotaryEncoder_Alps_EC11E-Switch_Vertical_H20mm,C7435302,1
Rotary_Encoder_R,ENC2,RotaryEncoder_Alps_EC11E-Switch_Vertical_H20mm,C7435302,1
SM6T6V8A,D2,D_SMB_Handsoldering,C511038,1
SPDIF OUT,J3,Pin_Header_Straight_1x02,C5360898,1
TLP2362,OC1,SO-5-6_4.55x3.7mm_P1.27mm,C37658,1
TLV75733PDBV,U10,SOT-23-5_HandSoldering,C485517,1
TPD3S014,U1,SOT-23-6_Handsoldering,C87384,1
USB,USB2,USB_C_Receptacle_G-Switch_GT-USB-7010ASV,C165948,1
USB_HOST,USB1,USB_A_Molex_67643_Horizontal,C2346,1
~,H8,MountingHole_M3,,1
~,H6,MountingHole_M3,,1
~,H4,MountingHole_M3,,1
~,H2,MountingHole_M3,,1
